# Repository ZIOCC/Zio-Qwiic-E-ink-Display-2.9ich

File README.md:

# Zio Qwiic E-Ink Display 2.9"

> This product can be available for purchase [here](https://www.smart-prototyping.com/%20Zio-Qwiic-E-ink-Display-I2C).

##### Description

An E-ink module is great, how about to make it even nicer? Here we go! Instead of using SPI protocol, we created this I2C E-ink display to join our Qwiic family. So you can just daisy chain this E-ink display just like the other Qwiic modules!

Nothing fancy here, we add a STM32 as the gateway, it can communicate with I2C system, then drive E-ink display to refresh content by SPI protocol.

In order to inherit the ultra low power consuming feature of the E-ink display, we let the STM32 IC go into deep sleep mode (2uA power consuming) and add an I2C chip that is used for waking STM32 up.

> This product can be available for purchase [here](https://www.smart-prototyping.com/Zio-E-Ink-Display-2-9-in-Black-White-Red).

Tired of using boring black and white E-ink display? Let’s add a spicy color to it! This is a 2.9 inch Red-Black-white E-ink display with 296x128 pixels resolution.

The red is good, but not always, because of the limitation of the E-ink display technology, the refresh time for Red E-ink display is much longer than Black-White version, this E-ink display refresh time is 12 secs! Let’s hope the technology will solve this soon, until then, enjoy this red E-ink first!

##### Usage:

* Price tag for supermarket, shop
* Industry controller device
* Low power Consumption product and project

###### About Zio
> Zio is a new line of open sourced, compact, and grid layout boards, fully integrated for Arduino and Qwiic ecosystem. Designed ideally for wearables, robotics, small-space limitations or other on the go projects. Check out other awesome Zio products [here](https://www.smart-prototyping.com/Zio).

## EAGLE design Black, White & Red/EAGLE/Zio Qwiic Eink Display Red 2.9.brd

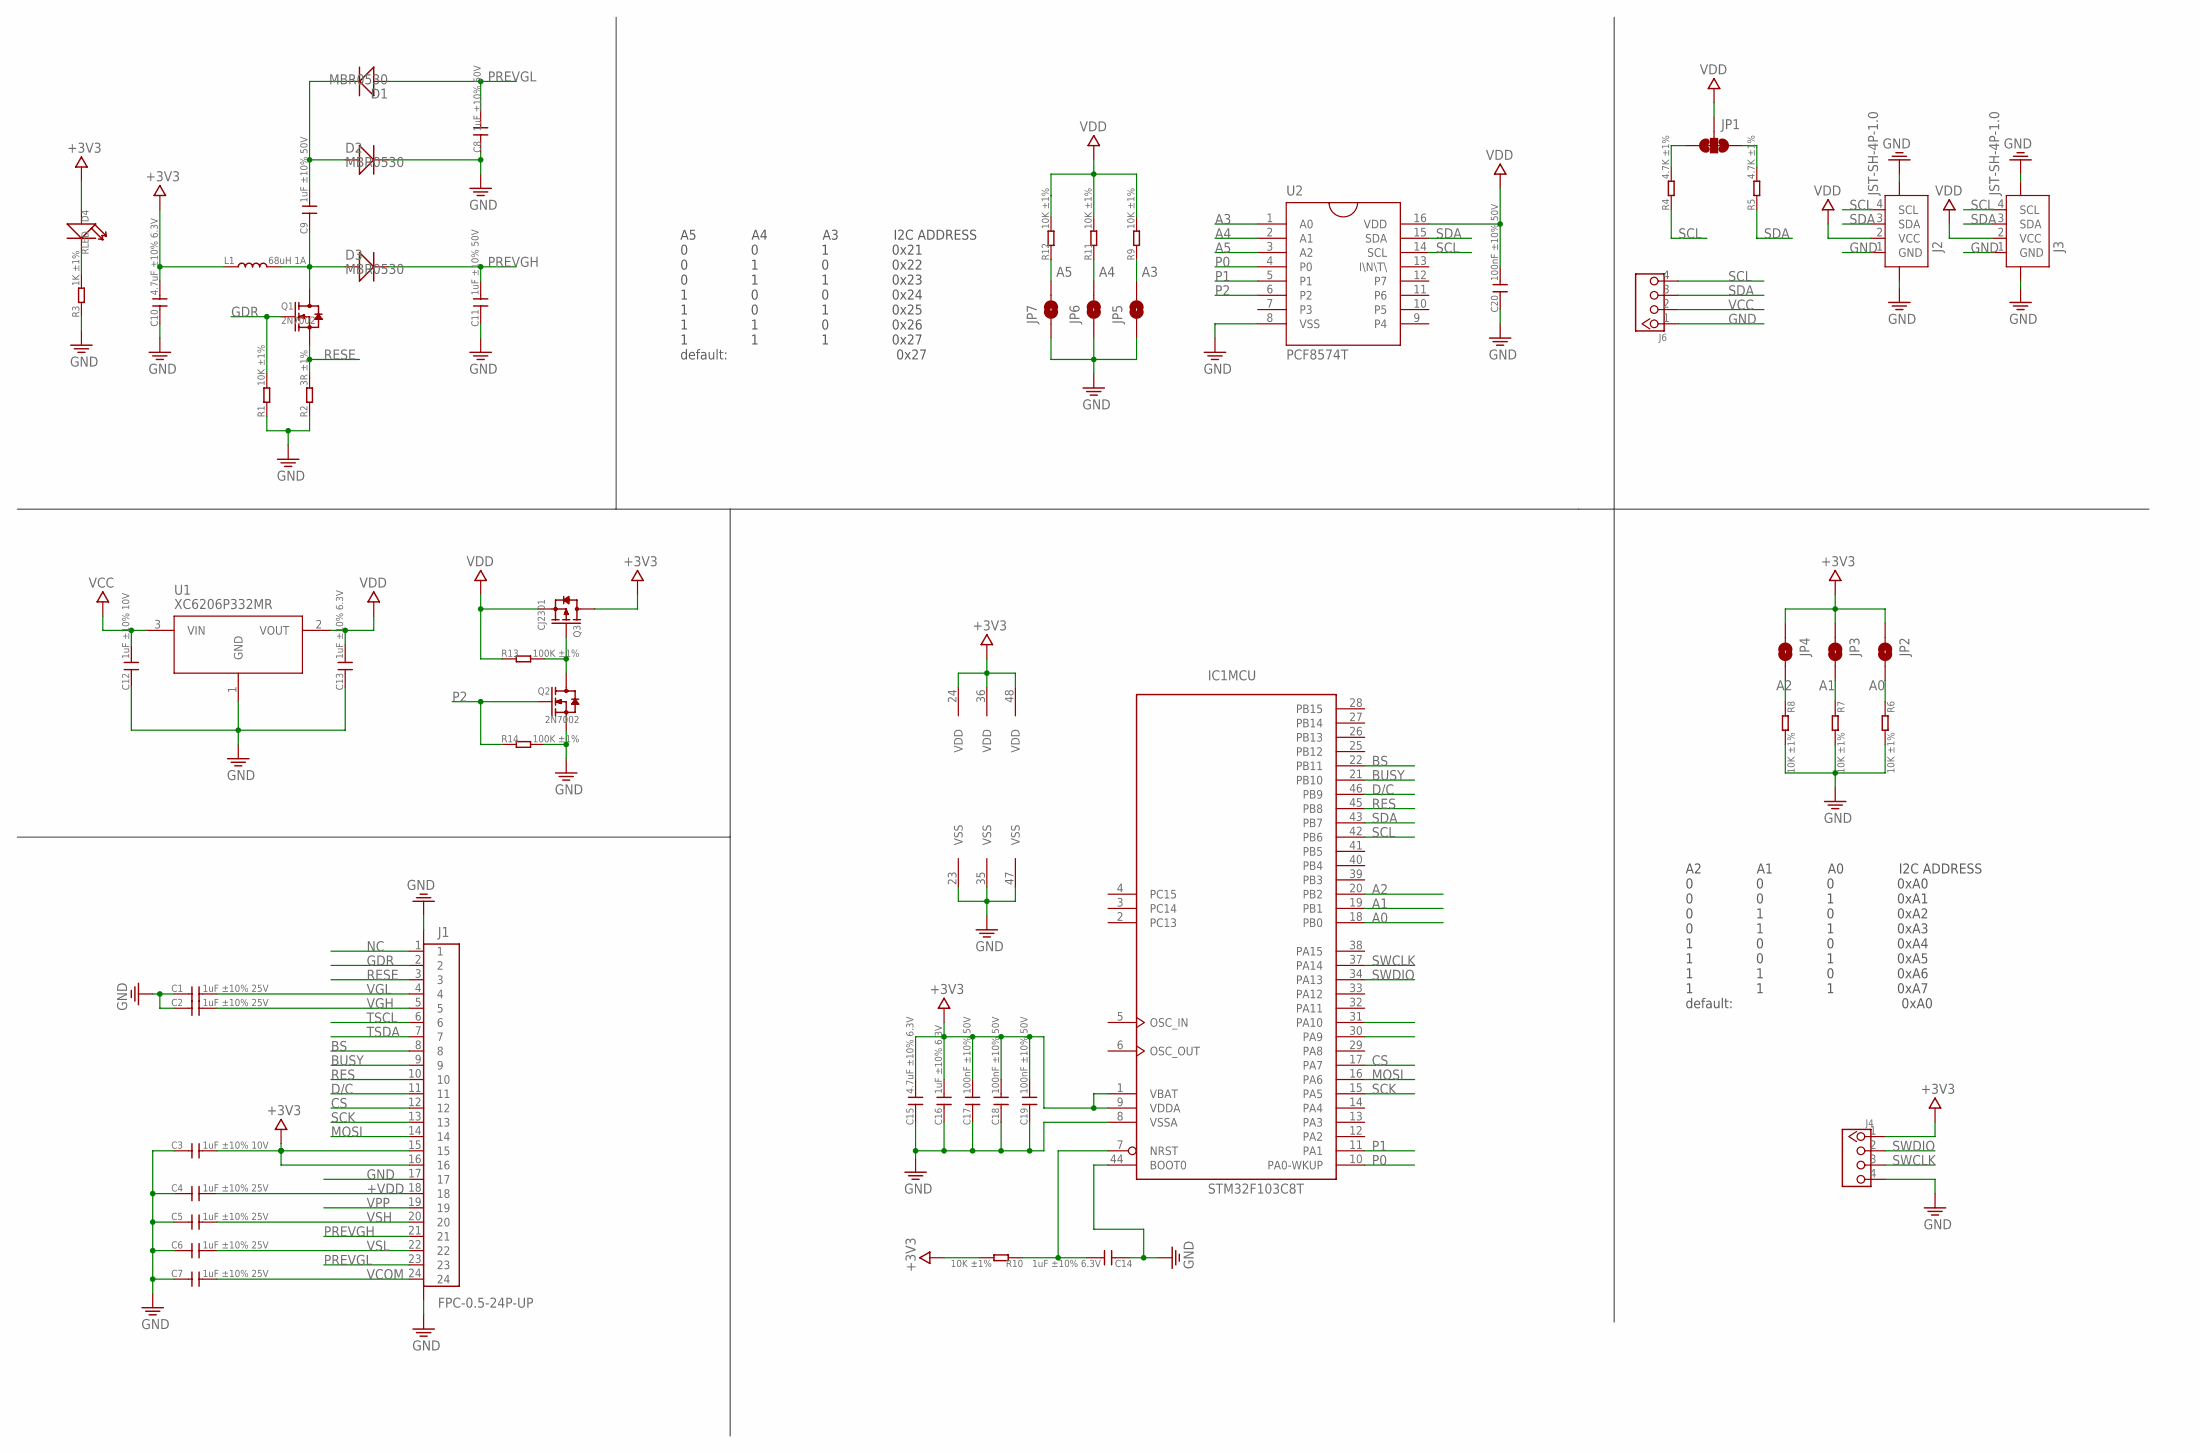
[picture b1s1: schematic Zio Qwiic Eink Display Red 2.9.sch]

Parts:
C1, C2, C4, C5, C6, C7: 1uF ±10% 25V; C0603
C3, C12: 1uF ±10% 10V; C0603
C8: 1uF ±10% 50V; 0603
C9, C11: 1uF ±10% 50V; C0603
C10, C15: 4.7uF ±10% 6.3V; C0603
C13, C14, C16: 1uF ±10% 6.3V; C0603
C17, C18, C19, C20: 100nF ±10% 50V; C0603
D1, D2, D3: MBR0530; SOD123
D4: RLED; LED-0603
IC1: STM32F103C8T; LQFP48
J1: FPC-0.5-24P-UP; FPC-0.5-24P_UP
J2, J3: JST-SH-4P-1.0; JST-SH-4P
J4: HEADER-4P-2.54-SMD; 4P-2.54-SMD-180
J6: HEADER-4P-60/35MIL; 4P-65/35MIL
JP1: SMT-JUMPER_3_2-NC_TRACE
JP2, JP3, JP4, JP5, JP6, JP7: JUMPER-SMT_2_NC_PASTE_NOCREM; SMT-JUMPER_2_NC_PASTE_SILK_NOCREM
L1: 68uH 1A; L3012
Q1, Q2: 2N7002; SOT23
Q3: CJ2301; SOT23
R1, R6, R7, R8, R9, R10, R11, R12: 10K ±1%; R0603
R2: 3R ±1%; R0603
R3: 1K ±1%; R0603
R4, R5: 4.7K ±1%; R0603
R13, R14: 100K ±1%; R0603
U1: XC6206P332MR; SOT23
U2: PCF8574T; SO16-W

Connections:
+3V3: C3.2, C10.2, C15.2, C16.2, C17.2, C18.2, C19.2, D4.+, IC1.1 (VBAT), IC1.9 (VDDA), IC1.24 (VDD), IC1.36 (VDD), IC1.48 (VDD), J1.15, J1.16, J4.1, JP2.1, JP3.1, JP4.1, L1.1, Q3.3 (D), R10.2
+VDD: C4.2, J1.18
A0: IC1.18 (PB0), JP2.2, R6.1
A1: IC1.19 (PB1), JP3.2, R7.1
A2: IC1.20 (PB2), JP4.2, R8.1
A3: JP5.2, R9.1, U2.1 (A0)
A4: JP6.2, R11.1, U2.2 (A1)
A5: JP7.2, R12.1, U2.3 (A2)
BS: IC1.22 (PB11), J1.8
BUSY: IC1.21 (PB10), J1.9
CS: IC1.17 (PA7), J1.12
D/C: IC1.46 (PB9), J1.11
GDR: J1.2, Q1.1 (G), R1.2
GND: C1.1, C2.1, C3.1, C4.1, C5.1, C6.1, C7.1, C8.1, C10.1, C11.1, C12.1, C13.1, C14.1, C15.1, C16.1, C17.1, C18.1, C19.1, C20.1, D2.-, IC1.8 (VSSA), IC1.23 (VSS), IC1.35 (VSS), IC1.44 (BOOT0), IC1.47 (VSS), J1.17, J1.25 (G1), J1.26 (G2), J2.1 (GND), J2.NC1 (5), J2.NC2 (6), J3.1 (GND), J3.NC1 (5), J3.NC2 (6), J4.4, J6.1, JP5.1, JP6.1, JP7.1, Q2.2 (S), R1.1, R2.1, R3.1, R6.2, R7.2, R8.2, R14.2, U1.1 (GND), U2.8 (VSS)
MOSI: IC1.16 (PA6), J1.14
unnamed: C9.2, D1.-, D2.+
unnamed: C9.1, D3.+, L1.2, Q1.3 (D)
unnamed: C14.2, IC1.7 (NRST), R10.1
unnamed: JP1.3, R4.2
unnamed: D4.-, R3.2
unnamed: JP1.1, R5.2
unnamed: Q2.3 (D), Q3.1 (G), R13.2
NC: J1.1
P0: IC1.10 (PA0-WKUP), U2.4 (P0)
P1: IC1.11 (PA1), U2.5 (P1)
P2: Q2.1 (G), R14.1, U2.6 (P2)
PREVGH: C11.2, D3.-, J1.21
PREVGL: C8.2, D1.+, J1.23
RES: IC1.45 (PB8), J1.10
RESE: J1.3, Q1.2 (S), R2.2
SCK: IC1.15 (PA5), J1.13
SCL: IC1.42 (PB6), J2.4 (SCL), J3.4 (SCL), J6.4, R4.1, U2.14 (SCL)
SDA: IC1.43 (PB7), J2.3 (SDA), J3.3 (SDA), J6.3, R5.1, U2.15 (SDA)
SWCLK: IC1.37 (PA14), J4.3
SWDIO: IC1.34 (PA13), J4.2
TSCL: J1.6
TSDA: J1.7
VCC: C12.2, J6.2, U1.3 (VIN)
VCOM: C7.2, J1.24
VDD: C13.2, C20.2, J2.2 (VCC), J3.2 (VCC), JP1.2, Q3.2 (S), R9.2, R11.2, R12.2, R13.1, U1.2 (VOUT), U2.16 (VDD)
VGH: C2.2, J1.5
VGL: C1.2, J1.4
VPP: J1.19
VSH: C5.2, J1.20
VSL: C6.2, J1.22

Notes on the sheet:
A2 A1 A0 I2C ADDRESS 0 0 0 0xA0 0 0 1 0xA1 0 1 0 0xA2 0 1 1 0xA3 1 0 0 0xA4 1 0 1 0xA5 1 1 0 0xA6 1 1 1 0xA7 default: 0xA0
A5 A4 A3 I2C ADDRESS 0 0 1 0x21 0 1 0 0x22 0 1 1 0x23 1 0 0 0x24 1 0 1 0x25 1 1 0 0x26 1 1 1 0x27 default: 0x27

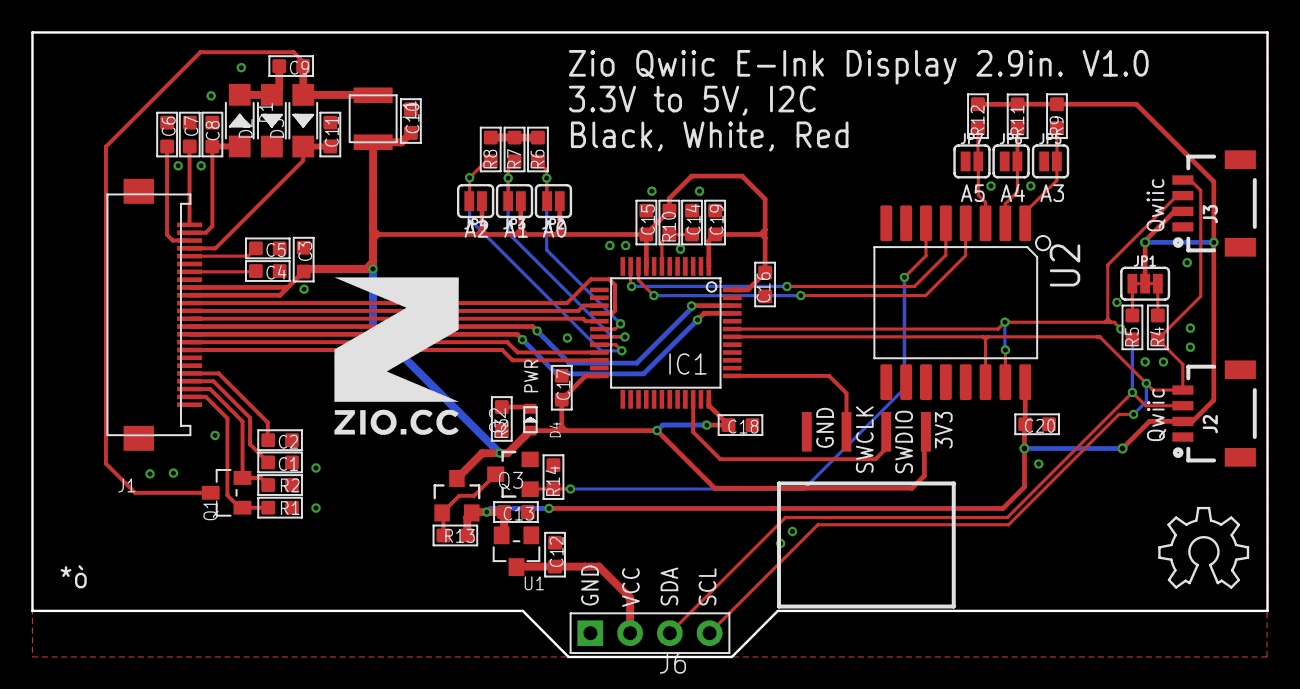
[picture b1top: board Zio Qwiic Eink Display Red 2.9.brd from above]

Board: 2 copper layers, 79.0 x 39.9 mm, 59 parts (0 on the bottom side), 41 nets.

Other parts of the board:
U$10: OSHW_6X200_NOTEXT
U$20: 10MM

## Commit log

2018-08-09 Create Black White
